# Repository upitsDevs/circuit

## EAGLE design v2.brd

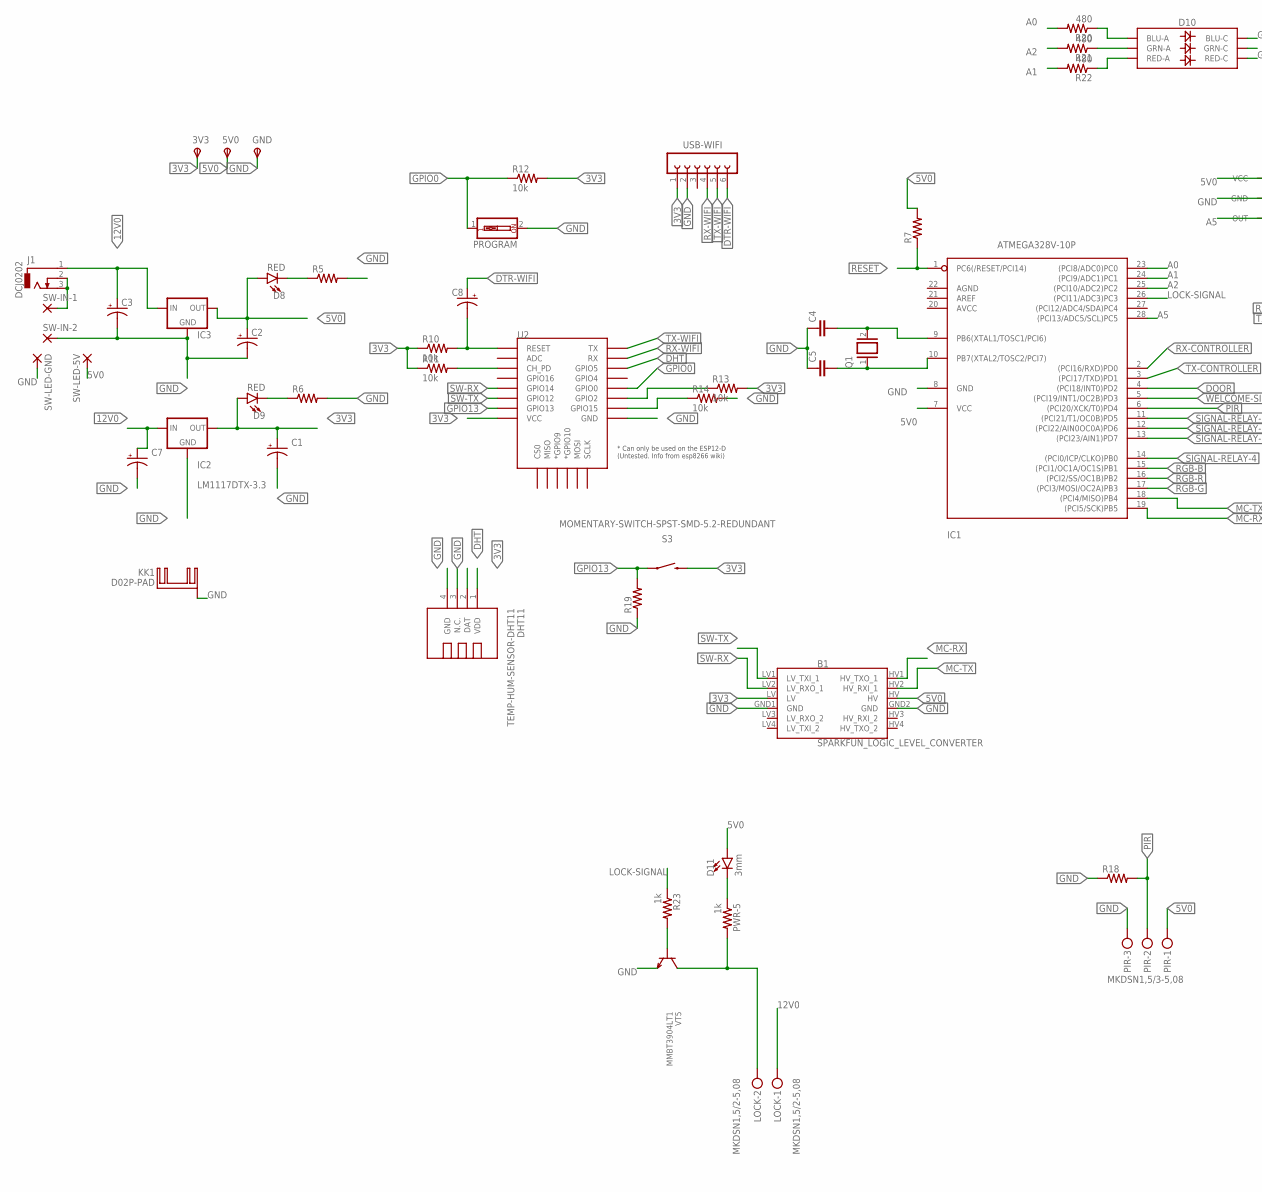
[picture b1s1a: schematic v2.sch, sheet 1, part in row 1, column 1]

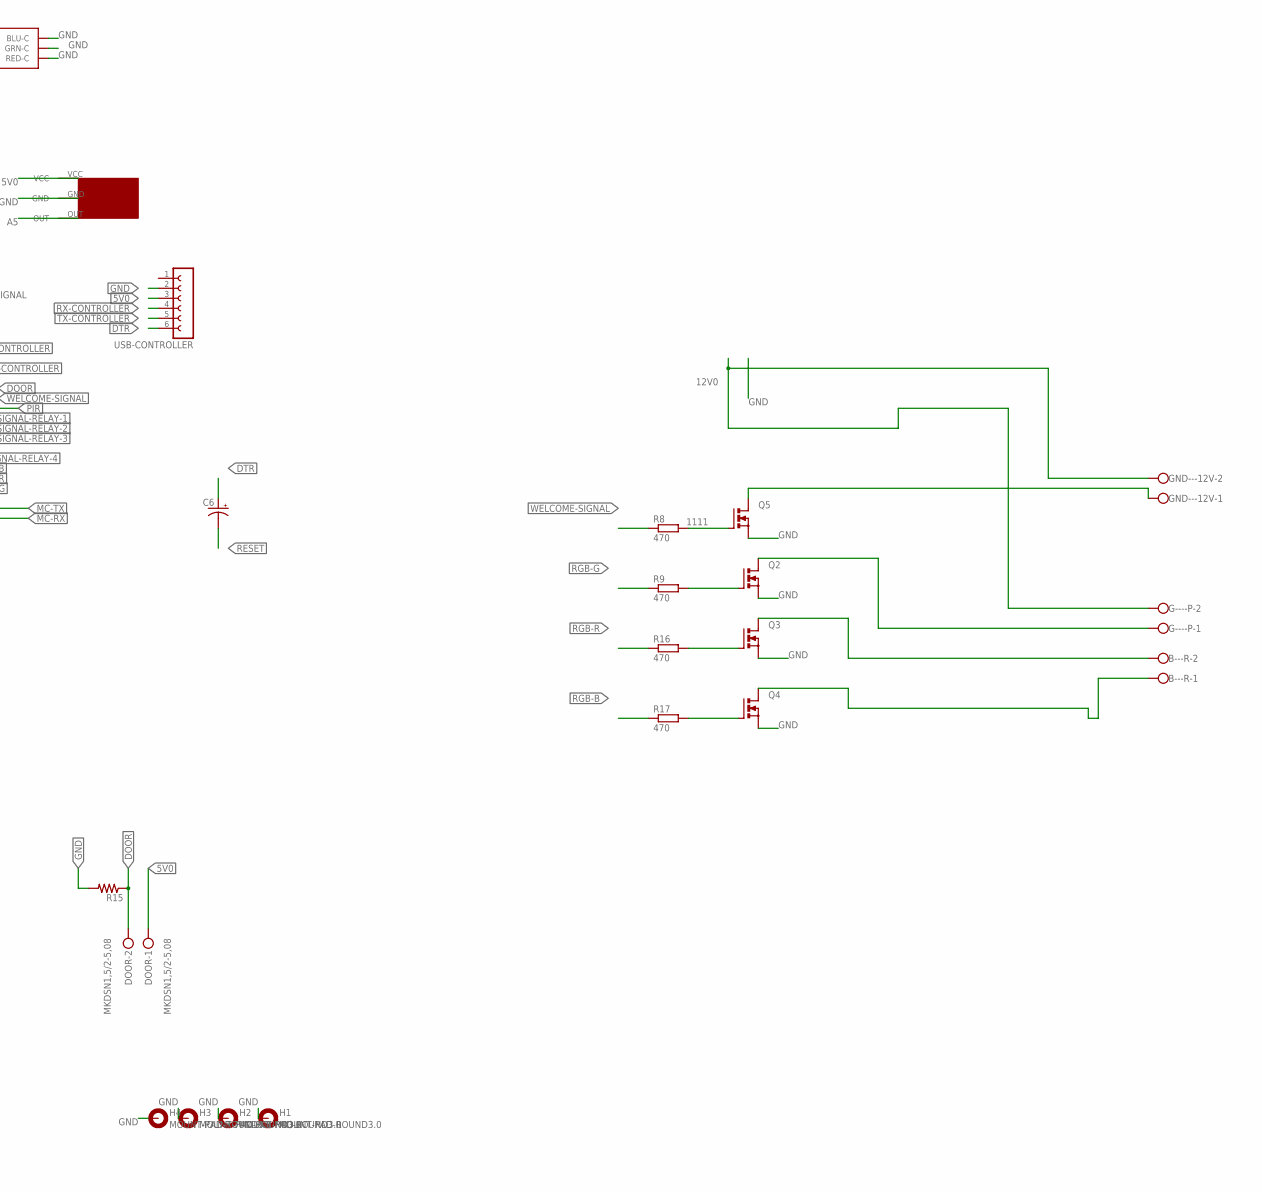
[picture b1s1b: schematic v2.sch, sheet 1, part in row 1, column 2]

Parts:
3V3, 5V0: TPSB2,54; B2,54
B1: SPARKFUN_LOGIC_LEVEL_CONVERTER
B---R: W237-102
C1, C2, C3, C7: CPOL-USE2.5-6; E2,5-6
C4, C5: C-EU025-024X044; C025-024X044
C6, C8: CPOL-USE2-5; E2-5
D8, D9: RED; LED-1206
D10: LED-RGBNO_IC; LED-TRICOLOR-5050
D11: 3mm; FKIT-LED-1206
DHT11: TEMP-HUM-SENSOR-DHT11
DOOR: MKDSN1,5/2-5,08
G----P: W237-102
GND: TPSB2,54; B2,54
GND---12V: W237-102
H1, H2, H3, H4: MOUNT-PAD-ROUND3.0; 3,0-PAD
IC1: ATMEGA328V-10P; DIL28-3
IC2: LM1117DTX-3.3; TO252
IC3: 78XXS
J1: DCJ0202
KK1: D02P-PAD; D02PA-PAD
LOCK: MKDSN1,5/2-5,08
PIR: MKDSN1,5/3-5,08
PROGRAM: SW_DIP-1; EDG-01
PWR-5: 1k; M1206
Q1: XTAL/S; QS
Q2, Q3, Q4, Q5: PMOSFET_NTO220BV; TO220BV
R5, R6, R7, R15, R18, R19: R-US_R1206; R1206
R8, R9, R16, R17: 470; R1206
R10, R11, R12, R13, R14: 10k; R1206
R20, R21, R22: 480; R1206
R23: 1k; M1206
S3: MOMENTARY-SWITCH-SPST-SMD-5.2-REDUNDANT; TACTILE_SWITCH_SMD_5.2MM
SW-IN-1, SW-IN-2: 2,54/1,1
SW-LED-5V: 2,54/1,1
SW-LED-GND: 2,54/1,1
U2: ESP12ESMD; ESP12E-SMD
U$2: VS1838B
USB-CONTROLLER: FE06-1; FE06
USB-WIFI: FE06-1; FE06
VT5: MMBT3904LT1; SOT23-BEC

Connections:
3V3: 3V3.TP, B1.LV, C1.+, D9.A, DHT11.1 (VDD), IC2.TAB (OUT), R10.1, R11.1, R12.2, R13.2, S3.3 (2), S3.4 (2), U2.VCC, USB-WIFI.1
5V0: 5V0.TP, B1.HV, C2.+, D8.A, D11.A, DOOR.1, IC1.7 (VCC), IC3.OUT, PIR.1, R7.2, SW-LED-5V.1, U$2.VCC, USB-CONTROLLER.3; also elsewhere on the board
12V0: C3.+, C7.+, G----P.2, GND---12V.2, IC2.2 (IN), IC3.IN, J1.1, LOCK.1
1111: Q5.G, R8.2
A0: IC1.23 ((PCI8/ADC0)PC0), R20.2
A1: IC1.24 ((PCI9/ADC1)PC1), R22.2
A2: IC1.25 ((PCI10/ADC2)PC2), R21.2
A5: IC1.28 ((PCI13/ADC5/SCL)PC5), U$2.OUT
DHT: DHT11.2 (DAT), U2.GPIO5
DOOR: DOOR.2, IC1.4 ((PCI18/INT0)PD2), R15.1
DTR: C6.+, USB-CONTROLLER.6
DTR-WIFI: C8.+, USB-WIFI.6
GND: B1.GND1 (GND), B1.GND2 (GND), C1.-, C2.-, C3.-, C4.1, C5.1, C7.-, D10.4 (BLU-C), D10.5 (RED-C), D10.6 (GRN-C), DHT11.3 (N.C.), DHT11.4 (GND), GND.TP, H1.B3,0, H2.B3,0, H3.B3,0, H4.B3,0, IC1.8 (GND), IC2.1 (GND), IC3.GND, KK1.B, PIR.3, PROGRAM.2, Q2.S, Q3.S, Q4.S, Q5.S, R5.2, R6.2, R14.2, R15.2, R18.1, R19.1, SW-IN-2.1, SW-LED-GND.1, U2.GND, U$2.GND, USB-CONTROLLER.2, USB-WIFI.2, VT5.E; also elsewhere on the board
GPIO0: PROGRAM.1, R12.1, U2.GPIO0
GPIO13: R19.2, S3.1, S3.2 (1), U2.GPIO13
MC-RX: B1.HV1 (HV_TXO_1), IC1.19 ((PCI5/SCK)PB5)
MC-TX: B1.HV2 (HV_RXI_1), IC1.18 ((PCI4/MISO)PB4)
unnamed: D10.3 (BLU-A), R20.1
unnamed: D10.1 (GRN-A), R21.1
unnamed: J1.2, J1.3, SW-IN-1.1
unnamed: D8.C, R5.1
unnamed: D9.C, R6.1
unnamed: C5.2, IC1.10 (PB7(XTAL2/TOSC2/PCI7)), Q1.1
unnamed: C4.2, IC1.9 (PB6(XTAL1/TOSC1/PCI6)), Q1.2
unnamed: Q2.G, R9.2
unnamed: Q3.G, R16.2
unnamed: Q4.G, R17.2
unnamed: G----P.1, Q2.D
unnamed: B---R.2, Q3.D
unnamed: B---R.1, Q4.D
unnamed: R14.1, U2.GPIO15
unnamed: GND---12V.1, Q5.D
unnamed: C8.-, R10.2, U2.RESET
unnamed: R11.2, U2.CH_PD
unnamed: R13.1, U2.GPIO2
unnamed: D10.2 (RED-A), R22.1
unnamed: D11.C, PWR-5.1
unnamed: LOCK.2, PWR-5.2, VT5.C
unnamed: IC1.26 ((PCI11/ADC3)PC3), R23.1
unnamed: R23.2, VT5.B
PIR: IC1.6 ((PCI20/XCK/T0)PD4), PIR.2, R18.2
RESET: C6.-, IC1.1 (PC6(/RESET/PCI14)), R7.1
RGB-B: IC1.15 ((PCI1/OC1A/OC1S)PB1), R17.1
RGB-G: IC1.17 ((PCI3/MOSI/OC2A)PB3), R9.1
RGB-R: IC1.16 ((PCI2/SS/OC1B)PB2), R16.1
RX-CONTROLLER: IC1.2 ((PCI16/RXD)PD0), USB-CONTROLLER.4
RX-WIFI: U2.RXD0 (RX), USB-WIFI.4
SIGNAL-RELAY-1: IC1.11 ((PCI21/T1/OC0B)PD5); also elsewhere on the board
SIGNAL-RELAY-2: IC1.12 ((PCI22/AIN0OC0A)PD6); also elsewhere on the board
SIGNAL-RELAY-3: IC1.13 ((PCI23/AIN1)PD7); also elsewhere on the board
SIGNAL-RELAY-4: IC1.14 ((PCI0/ICP/CLKO)PB0); also elsewhere on the board
SW-RX: B1.LV2 (LV_RXO_1), U2.GPIO14
SW-TX: B1.LV1 (LV_TXI_1), U2.GPIO12
TX-CONTROLLER: IC1.3 ((PCI17/TXD)PD1), USB-CONTROLLER.5
TX-WIFI: U2.TXD0 (TX), USB-WIFI.5
WELCOME-SIGNAL: IC1.5 ((PCI19/INT1/OC2B)PD3), R8.1

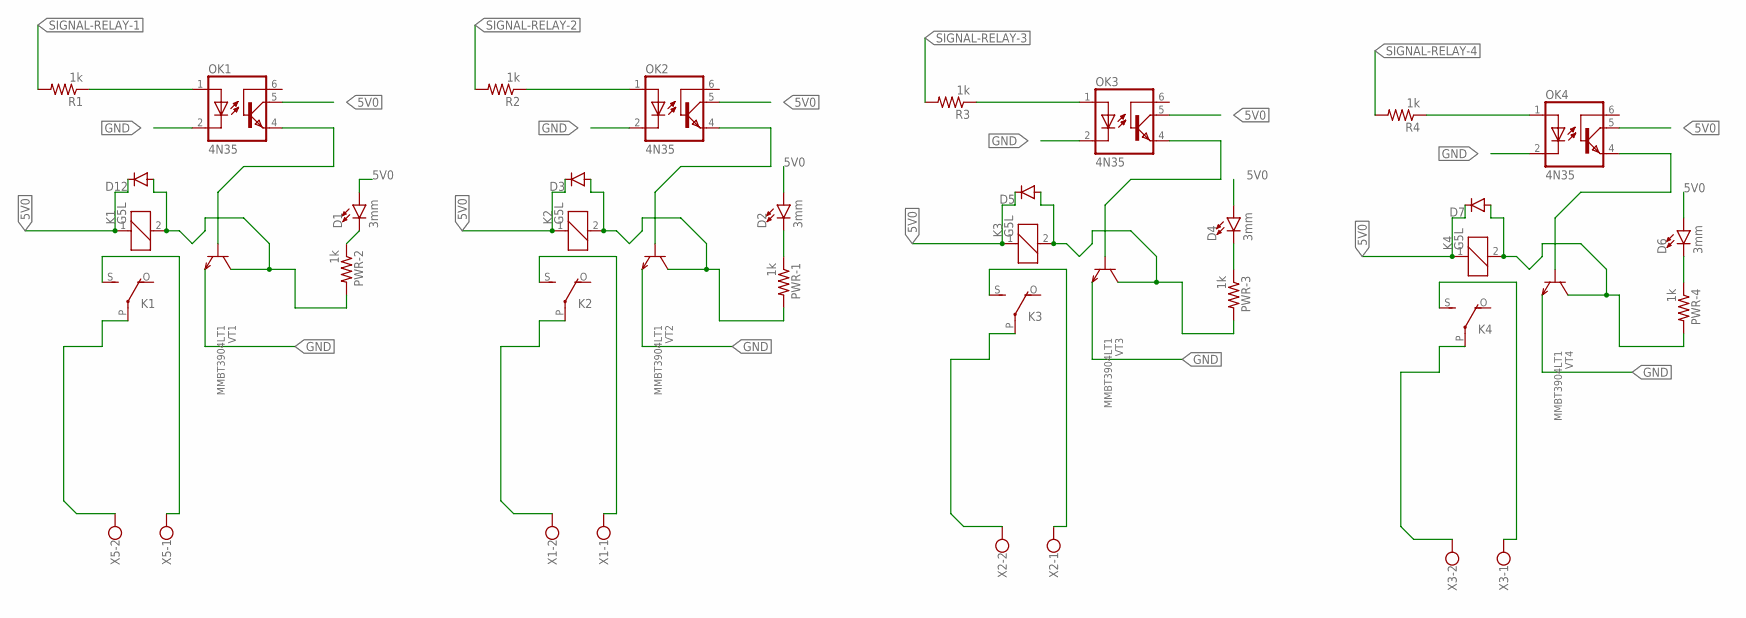
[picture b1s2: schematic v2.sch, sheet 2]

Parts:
D1, D2, D4, D6: 3mm; FKIT-LED-1206
D3, D5, D7, D12: DIODE-SOD80C; SOD80C
K1, K2, K3, K4: G5L; G5LE
OK1, OK2, OK3, OK4: 4N35; DIL06
PWR-1, PWR-2, PWR-3, PWR-4: 1k; M1206
R1, R2, R3, R4: 1k; M1206
VT1, VT2, VT3, VT4: MMBT3904LT1; SOT23-BEC
X1, X2, X3, X5: W237-102

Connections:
5V0: D1.A, D2.A, D3.C, D4.A, D5.C, D6.A, D7.C, D12.C, K1.1, K2.1, K3.1, K4.1, OK1.5 (COL), OK2.5 (COL), OK3.5 (COL), OK4.5 (COL); also elsewhere on the board
GND: OK1.2 (C), OK2.2 (C), OK3.2 (C), OK4.2 (C), VT1.E, VT2.E, VT3.E, VT4.E; also elsewhere on the board
unnamed: K1.P, X5.2
unnamed: K1.S, X5.1
unnamed: K2.P, X1.2
unnamed: OK1.4 (EMI), VT1.B
unnamed: D12.A, K1.2, PWR-2.2, VT1.C
unnamed: K2.S, X1.1
unnamed: OK1.1 (A), R1.1
unnamed: OK2.1 (A), R2.1
unnamed: D5.A, K3.2, PWR-3.2, VT3.C
unnamed: OK2.4 (EMI), VT2.B
unnamed: D2.C, PWR-1.1
unnamed: K3.P, X2.2
unnamed: K3.S, X2.1
unnamed: OK3.1 (A), R3.1
unnamed: OK3.4 (EMI), VT3.B
unnamed: D4.C, PWR-3.1
unnamed: K4.P, X3.2
unnamed: K4.S, X3.1
unnamed: OK4.1 (A), R4.1
unnamed: OK4.4 (EMI), VT4.B
unnamed: D6.C, PWR-4.1
unnamed: D1.C, PWR-2.1
unnamed: D7.A, K4.2, PWR-4.2, VT4.C
unnamed: D3.A, K2.2, PWR-1.2, VT2.C
SIGNAL-RELAY-1: R1.2; also elsewhere on the board
SIGNAL-RELAY-2: R2.2; also elsewhere on the board
SIGNAL-RELAY-3: R3.2; also elsewhere on the board
SIGNAL-RELAY-4: R4.2; also elsewhere on the board

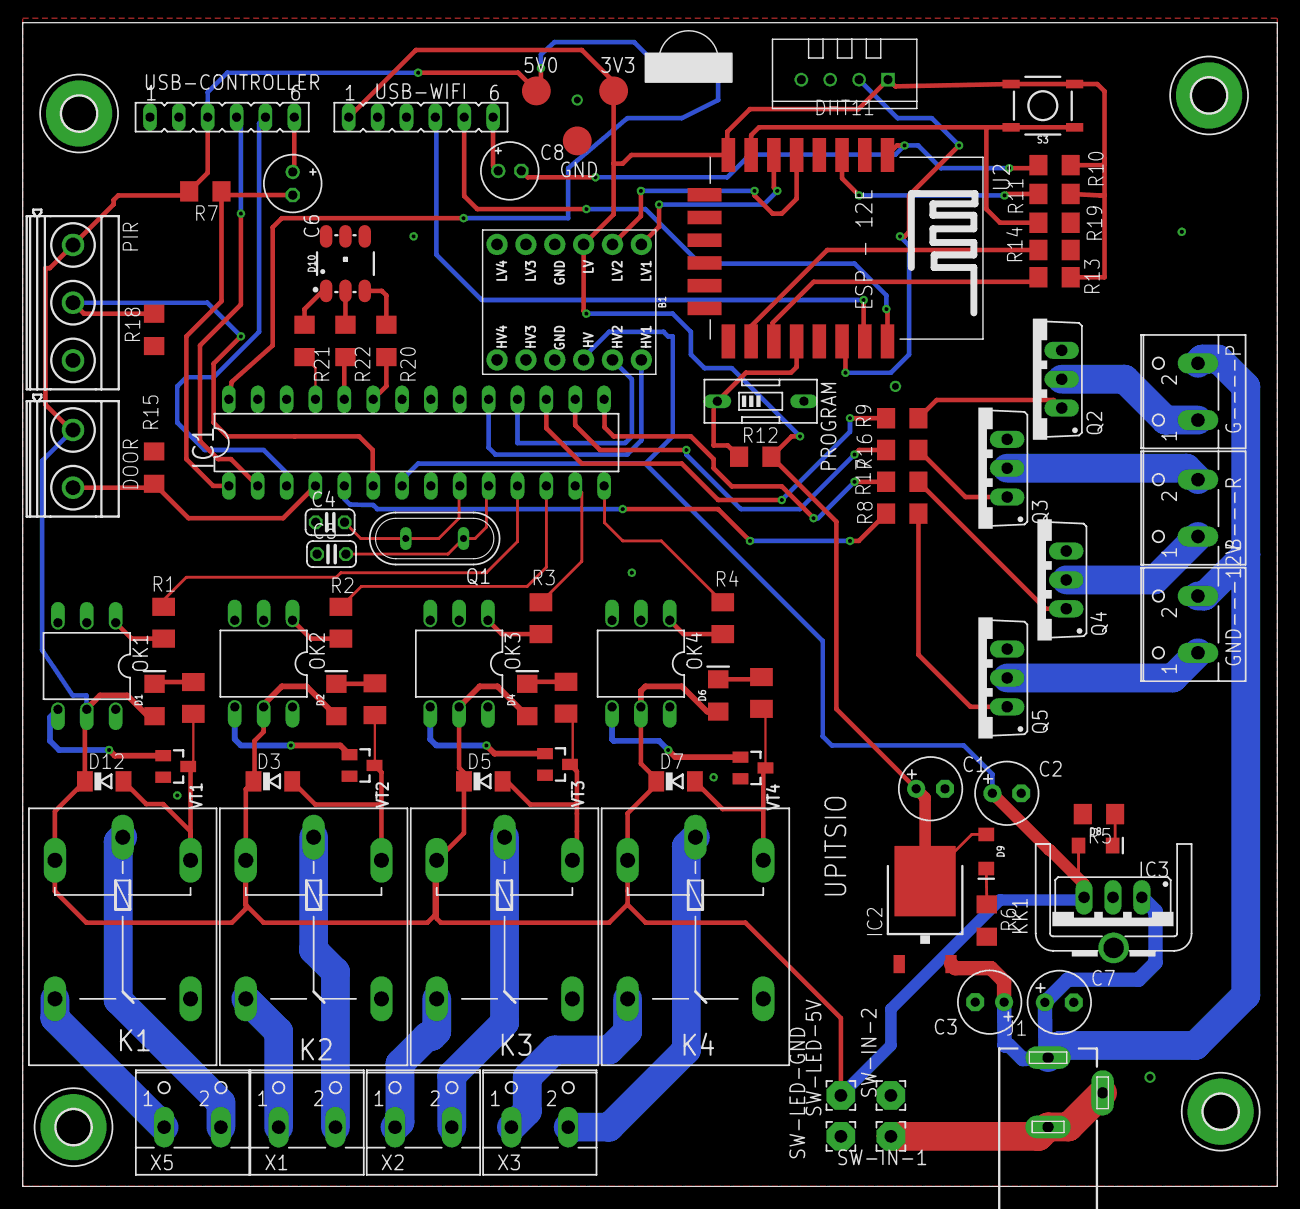
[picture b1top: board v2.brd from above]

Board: 2 copper layers, 110.4 x 102.4 mm, 95 parts (0 on the bottom side), 76 nets.

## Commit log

2019-01-05 initial
2019-01-05 initial 2

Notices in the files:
parts and their libraries:
SparkFun-Boards: Licensing: Creative Commons ShareAlike 4.0 International - https://creativecommons.org/licenses/by-sa/4.0
diy-modules: Released under the Creative Commons Attribution 4.0 International License: http://creativecommons.org/licenses/by/4.0
